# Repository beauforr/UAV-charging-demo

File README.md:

# UAV Charging Demo

Hardware demo based on [UAV-Based Charging Solution](https://github.com/jarnevanmulders/UAV-Based-Charging-Solution).

### Hardware Modules
- **`RX/`** — Receiver (IoT & PRU)
- **`TX/Inverter/`** — Half-bridge inverter (PTU)
- **`TX/Pre-regulator/`** — Pre-regulator (PTU)

---

### System Overview

### Experimental Setup

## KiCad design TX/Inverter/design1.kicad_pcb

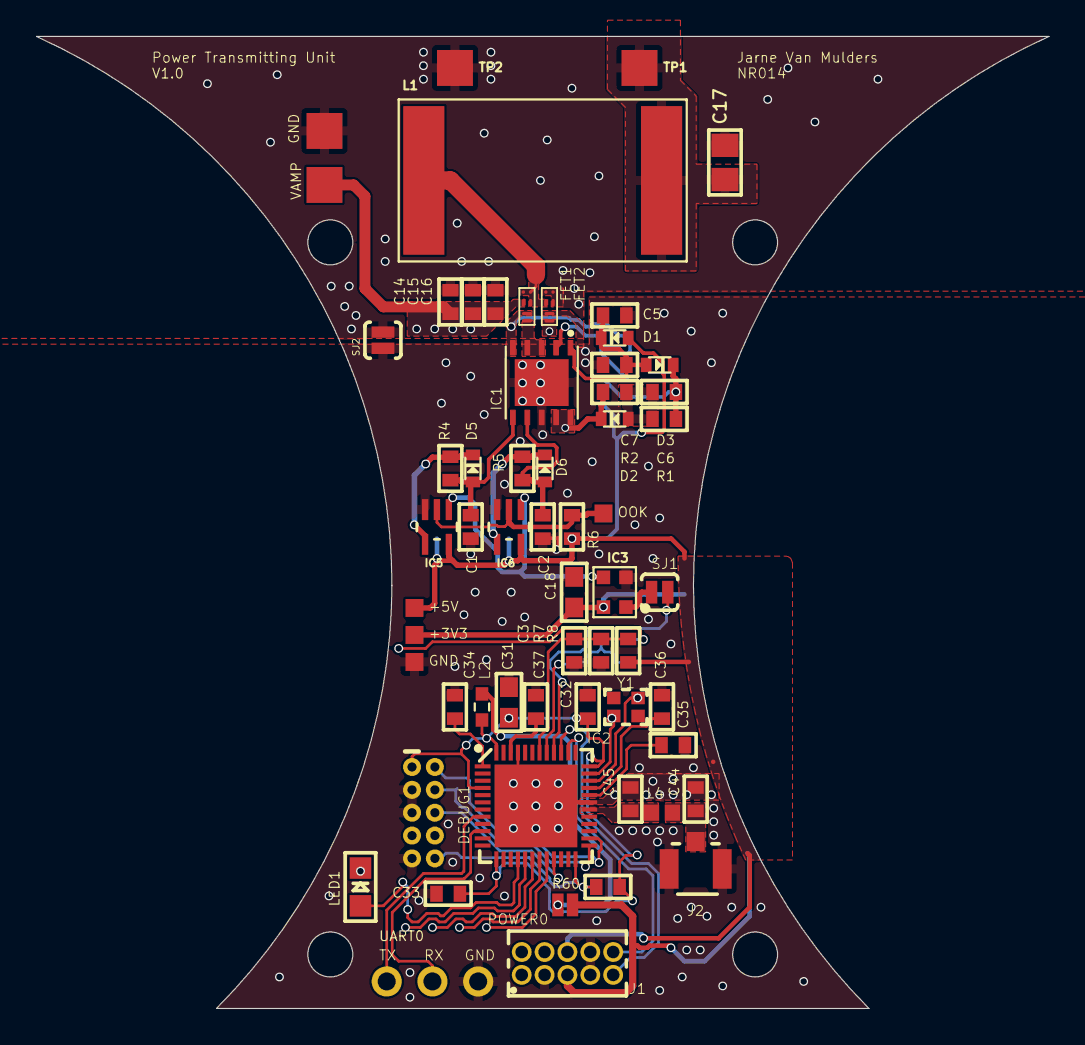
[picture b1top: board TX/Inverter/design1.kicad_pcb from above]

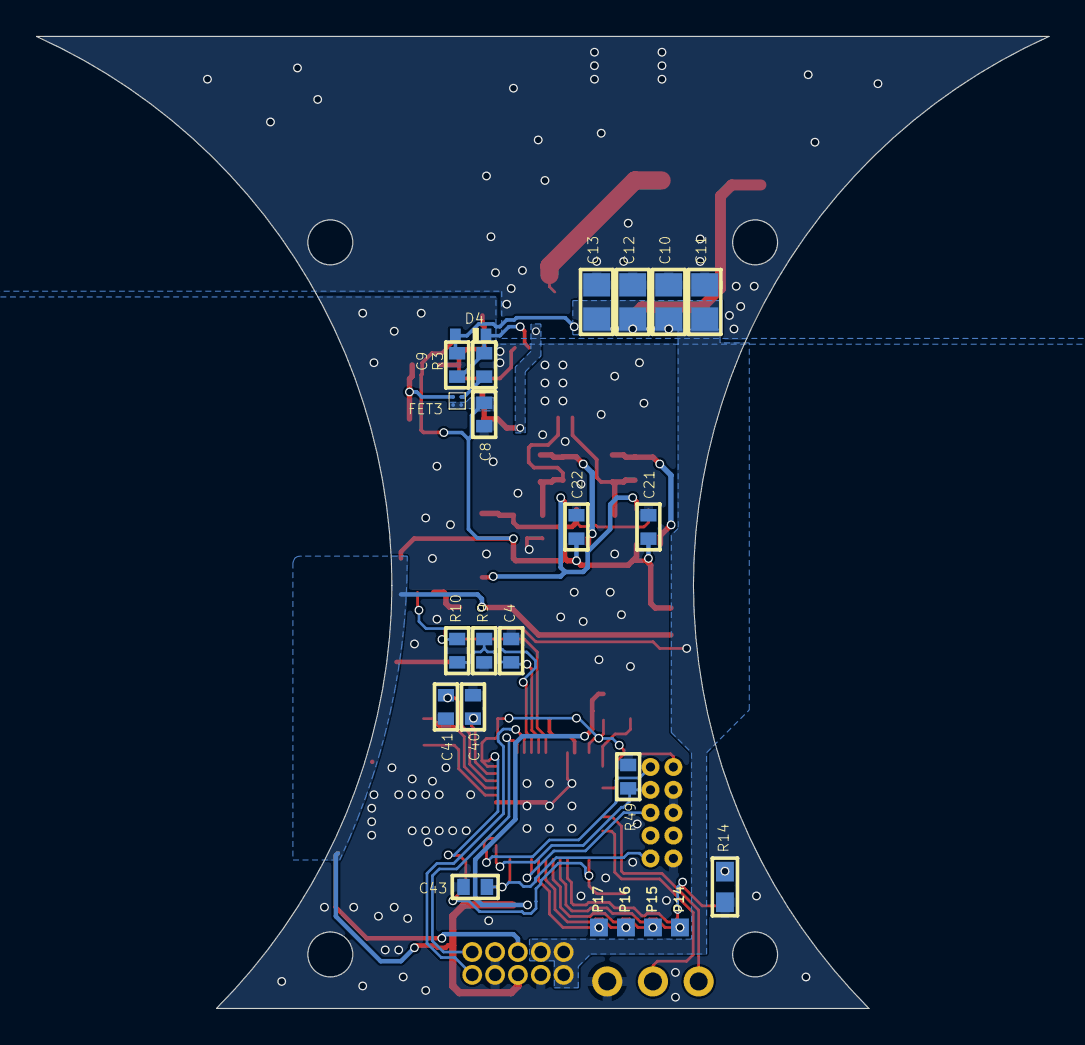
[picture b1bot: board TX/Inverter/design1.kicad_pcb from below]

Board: 2 copper layers, 56.3 x 54.0 mm, 83 parts (23 on the bottom side), 49 nets.

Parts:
C1, C2: 22p; 0402
C3, C4, C21, C22, C32, C33, C34, C43: 100n; 0402
C5, C8, C9, C37: 1u; 0402
C6, C7: 22n; 0402
C10, C11, C12, C13, C17: 1u; 0805
C14, C15, C16: 10n; 0402
C18: 100n; 0603
C31: 4u7; 0603
C35, C44: DNP; 0402
C36: 100p; 0402
C40, C41: 6p; 0402
C45: 0.8p; 0402
D1: BAT54K; SOD-523
D2, D3, D5, D6: RB751S40T1G; SOD-523
D4: CZRU52C5V1; SOD-523F
DEBUG1: CORTEX_DEBUGPTH; 2X5-PTH-1.27MM
FET1, FET2: EPC8010; BGA-8010
FET3: EPC2038; BGA-2038
IC1: LM5113SDX/NOPB; SON80P400X400X80-11N
IC2: NRF52832; QFN48-6X6MM-EXTENDED
IC3: DSC1001DI2-006.7800; 2.5X2.0MMPLASTICPACKAGE
IC5: 74LVC1G00GW; SOT65P210X110-5N
IC6: 74LVC1G08GW; SOT65P210X110-5N
J1: 62201021121
J2: 636101111001
L1: 2929SQ-501JE; 2929SQ-501
L2: 742792692; WE-CBF_0603(W=2.2)
L4: 3.9nH; 0402
LED1: CHIPLED_0805
P14, P15, P16, P17: TPTP10SQ; TP10SQ
POWER0: JUMPER-SMT_2_NO_NO-SILK; SMT-JUMPER_2_NO_NO-SILK
R1, R3: 27; 0402
R2: 20; 0402
R4, R5, R6: 180; 0402
R7, R8, R9, R49, R60: 10k; 0402
R10: 100k; 0402
R14: 220; 0603
SJ1, SJ2: SOLDERJUMPERNO; SJ_2S-NO
TP1, TP2, TP3, TP8: TPTP20SQ; TP20SQ
TP4, TP5, TP6, TP7: TPTP10SQ; TP10SQ
UART0: 1X03_ROUND
Y1: 32MHz; CRYSTAL-SMD-2.0X1.6MM

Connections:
+3V3: C18.1, IC3.4, J1.5, POWER0.1, TP6.TP
+4V7: C5.1, C7.1, D1.K, D3.A, IC1.1
+5V: C8.1, C21.1, C22.1, D1.A, FET3.2, FET3.4, IC5.5, IC6.5, J1.6, R6.1, R8.2, TP4.TP
AGND: C10.2, C11.2, C12.2, C13.2, C14.2, C15.2, C16.2, C17.2, FET2.3, FET2.5, FET2.6, SJ2.2, TP2.TP, TP8.TP
ANT: C45.1, IC2.30, L4.2
DEC4: C37.2, IC2.46
DEC5: C34.2, IC2.1
DEC6: C35.2, IC2.32
DEC8: C36.2, IC2.33
GBTST: C6.1, D3.K, FET3.1, R1.2
GL: D2.K, FET2.1, IC1.9, IC1.10, R2.1
GND: C1.2, C2.2, C3.2, C4.2, C5.2, C7.2, C8.2, C18.2, C21.2, C22.2, C31.2, C32.2, C33.2, C34.1, C35.1, C36.1, C37.1, C40.1, C41.1, C43.2, C44.2, C45.2, DEBUG1.3, DEBUG1.5, DEBUG1.9, FET2.2, IC1.8, IC1.11, IC2.31, IC2.45, IC2.EP, IC3.2, IC5.3, IC6.3, J1.3, J1.7, J1.8, J2.2, J2.3, R7.1, R9.1, R14.1, R49.1, SJ2.1, TP7.TP, UART0.3
GU: FET1.1, IC1.3, IC1.4
HSIG: C1.1, D5.A, IC1.6, R4.2
I2C_SCL: IC2.39, J1.9
I2C_SDA: IC2.38, J1.10
LED: IC2.16, LED1.A
LSIG: C2.1, D6.A, IC1.7, R5.2
unnamed: FET3.3, R3.1
unnamed: D5.K, IC5.4, R4.1
unnamed: IC3.1, SJ1.2
unnamed: D6.K, IC6.4, R5.1
unnamed: LED1.C, R14.2
unnamed: C6.2, D2.A, R1.1, R2.2
unnamed: C17.1, L1.2, TP1.TP
unnamed: L2.1, POWER0.2
OOK: IC5.2, IC6.2, R6.2, TP5.TP
OSC_CLK: IC3.3, IC5.1, IC6.1
OSC_ENABLE: IC2.40, SJ1.1
OUT: FET1.3, FET1.5, FET1.6, FET2.4, L1.1
OUT+5V: C9.1, D4.1, IC1.2, R3.2
OUT_GU: C9.2, D4.2, FET1.2, IC1.5
P06: IC2.8, UART0.1
P08: IC2.10, UART0.2
P14: IC2.17, P14.TP
P15: IC2.18, P15.TP
P16: IC2.19, P16.TP
P17: IC2.20, P17.TP
SWDCLK: DEBUG1.4, IC2.25, R49.2
SWDIO: DEBUG1.2, IC2.26
SWO/TDO: DEBUG1.6, IC2.21
UFL: C44.1, J2.1, L4.1
V-5V: C3.1, IC2.42, R7.2, R8.1
V-VAMP: C4.1, IC2.41, R9.2, R10.1
VAMP: C10.1, C11.1, C12.1, C13.1, C14.1, C15.1, C16.1, FET1.4, J1.1, J1.2, J1.4, R10.2, TP3.TP
VDD_BLE: C31.1, C32.1, C33.1, DEBUG1.1, IC2.4, IC2.13, IC2.36, IC2.48, L2.2, R60.1
XC1: C41.2, IC2.34, Y1.3
XC2: C40.2, IC2.35, Y1.1
~RESET: C43.1, DEBUG1.10, IC2.24, R60.2

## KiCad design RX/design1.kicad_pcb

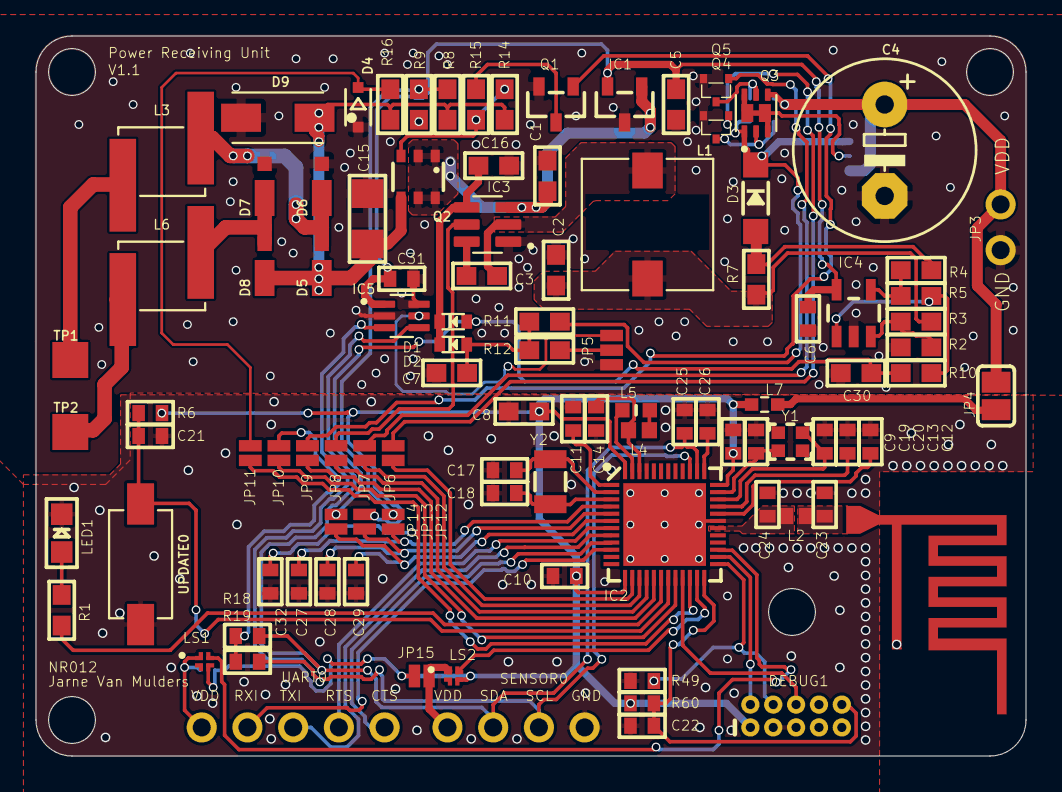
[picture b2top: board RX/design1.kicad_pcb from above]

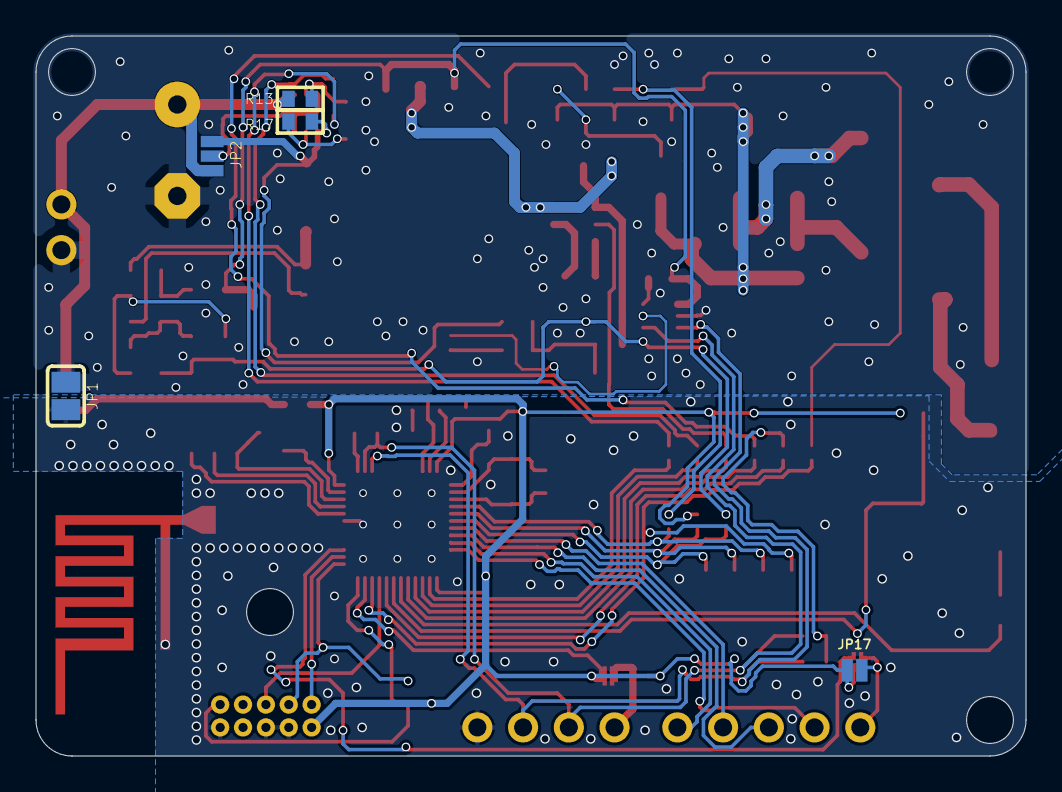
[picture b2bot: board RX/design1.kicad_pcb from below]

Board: 2 copper layers, 55.0 x 40.0 mm, 107 parts (5 on the bottom side), 76 nets.

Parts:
C1, C2, C5: 10u; 0603
C3, C7, C30: 100n; 0603
C4: LTO; E5-10,5
C6, C9, C10, C11, C21, C22, C27, C28, C29, C31, C32: 100n; 0402
C8: 4u7; 0603
C12: DNP; 0402
C13: 100p; 0402
C14: 1u; 0402
C15: 10u; 1206
C16: 100p; 0603
C17, C18: 15p; 0402
C19, C20: 6p; 0402
C23: 1.2p; 0402
C24: 0.8p; 0402
C25, C26: 12p; 0402
D1, D2: RB751S40T1G; SOD-523
D3: 512-SS24FL; SOD-123
D4: MM3Z3V0T1G; SOD323-R
D5, D6, D7, D8: PD3S160; POWERDI323
D9: SMAJ30A; DIOM5026X229N
DEBUG1: CORTEX_DEBUGPTH; 2X5-PTH-1.27MM
IC1: AP7381-33SA-7; SOT23-R
IC2: QFN48-6X6MM-EXTENDED
IC3: TPS54308DDCR; SOT95P280X110-6N
IC4: MCP6486T-E/OT; SOT23-5
IC5: TPL0401A-10DCKR; SOT65P210X110-6N
JP1, JP4: SOLDERJUMPER_REFLOW_NOPASTE
JP2, JP5: JUMPER-SMT_3_NO_NO-SILK; SMT-JUMPER_3_NO_NO-SILK
JP3: 1X02_ROUND
JP6, JP7, JP8, JP9, JP10, JP11, JP12, JP13, JP14, JP15, JP17: JUMPER-SMT_2_NO_NO-SILK; SMT-JUMPER_2_NO_NO-SILK
L1: 10uH; WE-PD_7332_7345_PLASTIC_BASE
L2: 3.9nH; 0402
L3, L6: WE-CAIR_4248
L4: 15nH; 0402
L5: 10uH; _0603MP
L7: 742792692; WE-CBF_0603(W=2.2)
LED1: CHIPLED_0805
LS1, LS2: MIC94081YFT-TR; IC_MIC94081YFT-TR
Q1: BSS138; SOT23-R
Q2: SI3481DV; TSOP-6.PAC
Q3: PMDPB55XP; SON65P200X200X65-8N
Q4, Q5: DMG1012T; SOT523-3
R1: 220; 0603
R2, R5: 56k; 0603
R3, R4: 1k2; 0603
R6, R49, R60: 10k; 0402
R7: R020; 0603
R8: 220k; 0603
R9, R14: 10k; 0603
R10: 100k; 0603
R11: 2k2; 0603
R12: 1k5; 0603
R13, R17: 100k; 0402
R15: 15k; 0603
R16: 1k; 0603
R18, R19: 4k7; 0402
SENSOR0: 1X04_ROUND
TP1, TP2: TPTP20SQ; TP20SQ
U$18: BLE-ANT; ANT-2G4
UART0: 1X05_ROUND
UPDATE0: 434111043826
Y1: 32MHz; CRYSTAL-SMD-2.0X1.6MM
Y2: 32.768kHz; CRYSTAL-SMD-3.2X1.5MM

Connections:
3.3V: C5.1, C6.1, C31.1, IC1.2, IC4.5, IC5.1
ADC1: JP12.2, R8.2, R9.1
AGND: C1.2, C2.2, C4.-, C5.2, C6.2, C7.2, C15.2, C16.1, C30.1, C31.2, D4.A, D6.A, D7.A, D9.A, IC1.3, IC3.1, IC4.2, IC5.2, IC5.6, JP1.1, JP3.2, JP5.1, Q1.2, Q4.2, Q5.2, R2.1, R9.2
ANT: C24.1, IC2.30, L2.2
BUCK-OUT-1: C2.1, L1.2, R3.2, R7.2
BUCK-OUT-2: D3.A, R4.2, R7.1
BUCK_EN: IC3.5, JP8.2
DCC: IC2.47, L5.1
DEC4: C14.2, IC2.46, L4.2
DEC5: C11.2, IC2.1
DEC6: C12.2, IC2.32
DEC8: C13.2, IC2.33
DIGI-POT: IC5.5, JP5.3
EN1: JP6.2, Q4.1
EN2: JP7.2, Q5.1
EN_MDM: IC2.27, LS1.4
EN_SENS: IC2.23, LS2.4
FB: C16.2, D1.K, D2.K, IC3.4
GND: C8.2, C9.2, C10.2, C11.1, C12.1, C13.1, C14.1, C17.2, C18.2, C19.1, C20.1, C21.2, C22.2, C23.2, C24.2, C25.2, C26.2, C27.2, C28.2, C29.2, C32.2, DEBUG1.3, DEBUG1.5, DEBUG1.9, IC2.31, IC2.45, IC2.EP, JP1.2, LED1.C, LS1.2, LS2.2, R49.1, SENSOR0.4, U$18.2, UPDATE0.1
I2C_PULLUP: JP10.2, R18.1, R19.1
I2C_SCL: IC2.39, IC5.3, R19.2, SENSOR0.3
I2C_SDA: C25.1, IC2.38, IC5.4, R18.2, SENSOR0.2
LED: IC2.18, R1.2
MIFA: C23.1, L2.1, U$18.1
unnamed: JP2.2, Q3.3, Q3.6, Q3.7, Q3.8
unnamed: C3.1, IC3.6
unnamed: C3.2, IC3.2, L1.1
unnamed: Q1.3, R15.2
unnamed: Q2.3, R14.2, R15.1
unnamed: JP5.2, R12.2
unnamed: JP4.2, L7.1
unnamed: IC4.4, R4.1, R5.1
unnamed: IC4.3, R2.2, R3.1
unnamed: L6.1, TP2.TP
unnamed: L3.1, TP1.TP
unnamed: D5.A, D6.C, L3.2
unnamed: D7.C, D8.A, L6.2
unnamed: Q3.2, Q4.3, R17.2
unnamed: Q3.5, Q5.3, R13.2
unnamed: LED1.A, R1.1
unnamed: C26.1, IC2.37
unnamed: L4.1, L5.2
OPAMP-OUT: IC4.1, R5.2, R10.1
P00: C17.1, IC2.2, Y2.P$2
P01: C18.1, IC2.3, Y2.P$1
P02: C27.1, IC2.4, JP12.1
P03: C28.1, IC2.5, JP13.1
P04: C29.1, IC2.6, JP14.1
P05: IC2.7, UART0.4
P06: IC2.8, UART0.3
P07: IC2.9, UART0.5
P08: IC2.10, UART0.2
P11: IC2.14, JP6.1
P12: IC2.15, JP7.1
P13: IC2.16, JP8.1
P14: IC2.17, JP9.1
P16: C21.1, IC2.19, R6.1, UPDATE0.2
P17: IC2.20, JP10.1
P19: C32.1, IC2.22, JP11.1
PG: JP9.2, Q1.1
SWDCLK: DEBUG1.4, IC2.25, R49.2
SWDIO: DEBUG1.2, IC2.26
SWO/TDO: DEBUG1.6, IC2.21
V-ICHG: C30.2, D1.A, JP14.2, R10.2
V-VCHG: C7.1, D2.A, R11.1, R12.1
VCHG: C4.+, JP2.3, JP3.1, JP4.1, Q3.4, R13.1
VDD_BLE: C8.1, C9.1, C10.1, DEBUG1.1, IC2.13, IC2.36, IC2.48, JP13.2, JP15.1, JP17.1, L7.2, LS1.3, LS2.3, R6.2, R60.1
VDD_MDM: JP17.2, LS1.1, UART0.1
VDD_SENS: JP15.2, LS2.1, SENSOR0.1
VDD_WPT: C15.1, D5.C, D8.C, D9.C, Q2.4, R8.1, R14.1, R16.1
VIN: C1.1, IC1.1, IC3.3, Q2.1, Q2.2, Q2.5, Q2.6
VMEAS: D3.C, JP2.1, Q3.1, R11.2, R17.1
WAKE-UP: D4.C, JP11.2, R16.2
XC1: C20.2, IC2.34, Y1.3
XC2: C19.2, IC2.35, Y1.1
~RESET: C22.1, DEBUG1.10, IC2.24, R60.2

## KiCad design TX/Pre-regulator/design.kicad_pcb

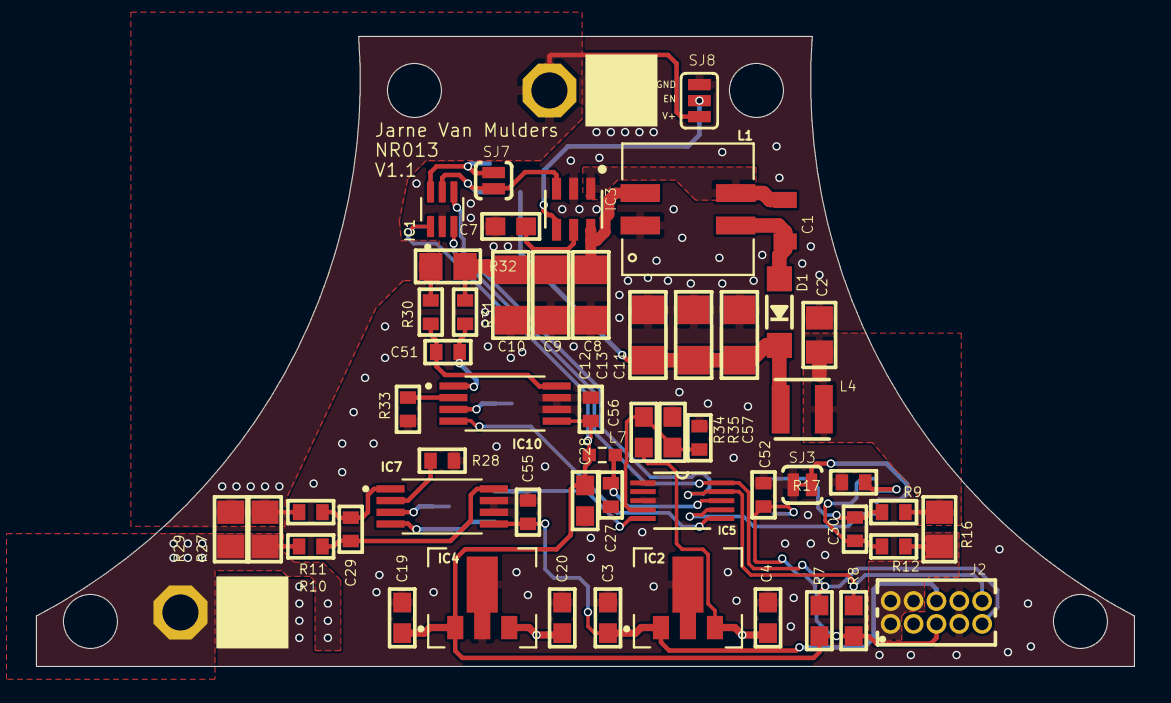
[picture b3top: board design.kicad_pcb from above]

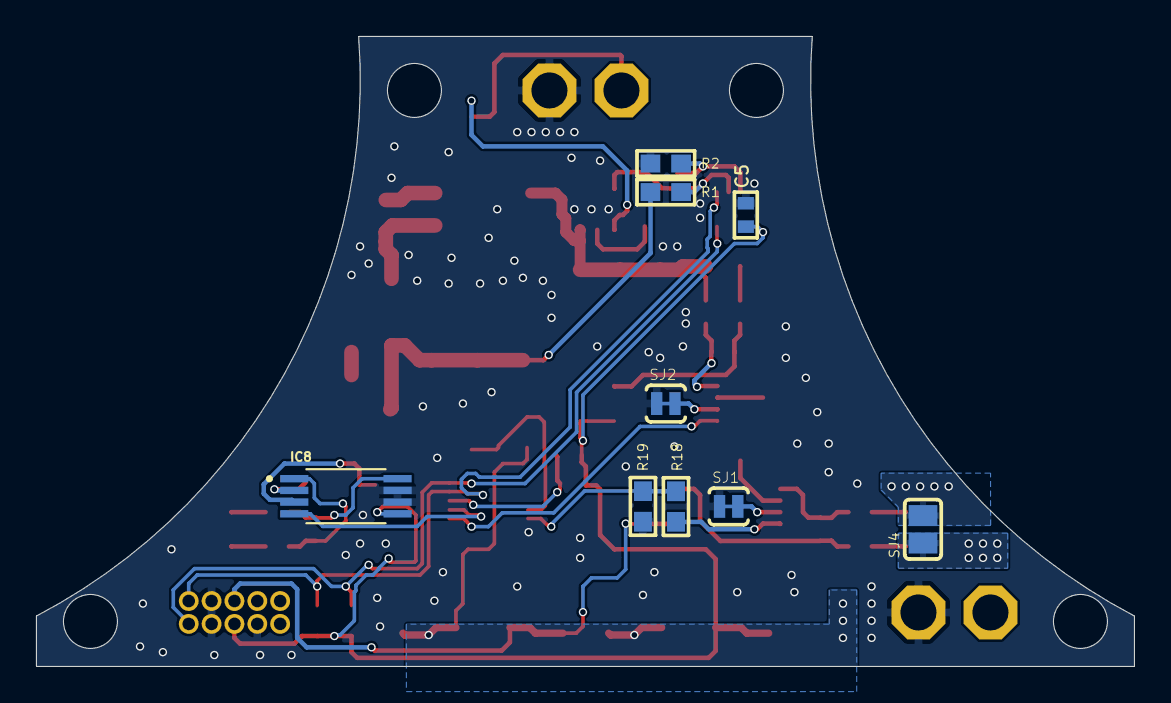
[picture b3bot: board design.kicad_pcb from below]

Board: 2 copper layers, 61.0 x 35.0 mm, 65 parts (9 on the bottom side), 35 nets.

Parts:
C1: 1u; WCAP-CSGP_0805_WAVE
C2: 10u; 0805
C3, C4, C19, C20, C28: 10u; 0603
C5, C27, C29, C30, C51, C52, C55, C56, C57: 100n; 0402
C7: 1u; 0603
C8, C9, C10, C11, C12, C13: 10u; 1206
D1: SS34; SOD-123
IC1: TPL0401A-10DCKR; SOT65P210X110-6N
IC2: AP7381-50Y-13; FOOT_XC6201P332PR-G
IC3: LT8330; TSOT-23_S6
IC4: AP7381-33Y-13; FOOT_XC6201P332PR-G
IC5: ADS1115IDGST; SOP50P490X110-10N
IC7, IC8, IC10: TSC1031; SOP65P640X120-8N
J2: 62201021121
L1: 744877100; WE-DD_7345
L4: 2u2; WE-LQS_3015
L7: 742792692; WE-CBF_0603(W=2.2)
R1, R35: 10k; 0603
R2: DNP; 0603
R7, R8: 4k7; 0603
R9, R10, R11, R12, R30, R31: 100; 0402
R16, R29, R32: 0.01; 0805
R17, R28, R33: 1k; 0402
R18, R34: 100k; 0603
R19: 47k; 0603
R27: DNP; 0805
SJ1, SJ2, SJ3: SOLDERJUMPERTRACE; SJ_2S-TRACE
SJ4: SOLDERJUMPER_REFLOW
SJ7: SOLDERJUMPERNO; SJ_2S-NO
SJ8: SJ_3
U2, U3: HOLE

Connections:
+3V3: C5.1, C19.1, C28.1, C52.1, C56.1, IC1.1, IC4.1, IC8.5, IC10.5, J2.5, L7.1, R7.1, R8.1
+5V: C3.1, C55.1, IC2.1, IC7.5, J2.6
AGND: C2.2, C3.2, C4.2, C5.2, C7.2, C8.2, C9.2, C10.2, C11.2, C12.2, C13.2, C19.2, C20.2, C27.2, C28.2, C52.2, C55.2, C56.2, C57.2, IC1.2, IC2.2, IC2.2.1, IC3.2, IC4.2, IC4.2.1, IC5.1, IC5.3, IC7.6, IC7.7, IC8.6, IC8.7, IC10.6, IC10.7, J2.3, J2.7, J2.8, L1.1, R2.1, R17.2, R19.1, R28.2, R33.2, R35.1, SJ1.1, SJ2.1, SJ3.1, SJ8.1, U2.2, U3.2
AIN0: C57.1, IC5.4, R34.1, R35.2
AIN1: IC5.5, R18.1, R19.2
AIN2: IC5.6, IC10.4
AIN3: IC5.7, IC8.4
I2C_SCL: IC1.3, IC5.10, J2.9, R7.2
I2C_SDA: IC1.4, IC5.9, J2.10, R8.2
LT_SW: C1.2, IC3.1, L1.3
unnamed: C30.1, IC8.1, R12.1
unnamed: C27.1, IC5.8, L7.2
unnamed: C7.1, IC3.5
unnamed: C1.1, D1.A, L1.2
unnamed: C11.1, C12.1, C13.1, D1.C, L4.1, R1.2
unnamed: IC3.4, SJ8.2
unnamed: C30.2, IC8.8, R9.1
unnamed: IC8.3, SJ3.2
unnamed: IC8.2, R17.1
unnamed: IC1.6, R2.2, SJ7.1
unnamed: IC7.3, SJ1.2
unnamed: C29.1, IC7.1, R11.1
unnamed: C29.2, IC7.8, R10.1
unnamed: C51.1, IC10.1, R31.1
unnamed: C51.2, IC10.8, R30.1
unnamed: IC7.2, R28.1
unnamed: IC10.3, SJ2.2
unnamed: IC10.2, R33.1
SEPIC_FB: IC1.5, IC3.3, R1.1, SJ7.2
UAV_BAT: C4.1, C20.1, IC2.3, IC4.3, R10.2, R27.1, R29.1, R34.2, SJ4.1, U2.1
UAV_BAT_1: R11.2, R27.2, R29.2, R30.2, R32.1, SJ4.2, SJ8.3, U3.1
VAMP: J2.1, J2.2, J2.4, R12.2, R16.2
VOUT_AIN1: IC7.4, R18.2
V_SEPIC_IN: C8.1, C9.1, C10.1, IC3.6, L1.4, R31.2, R32.2
V_SEPIC_OUT: C2.1, L4.2, R9.2, R16.1
